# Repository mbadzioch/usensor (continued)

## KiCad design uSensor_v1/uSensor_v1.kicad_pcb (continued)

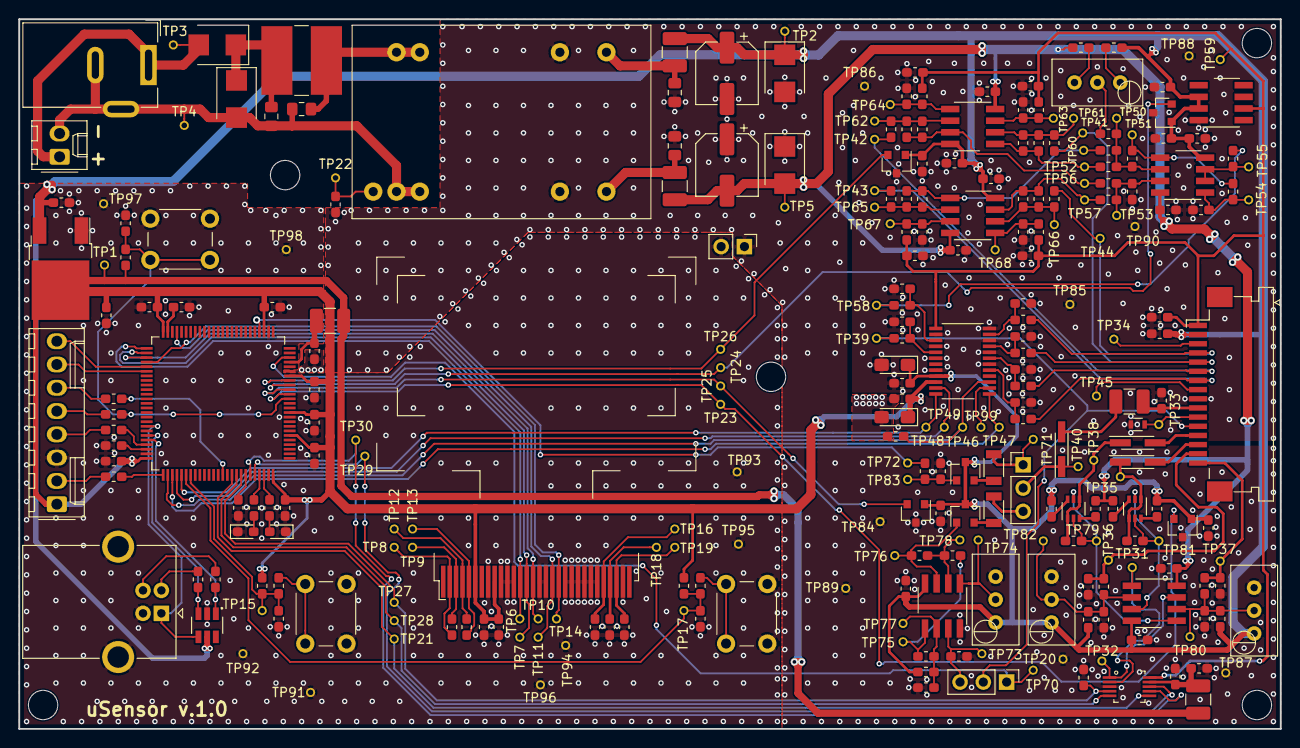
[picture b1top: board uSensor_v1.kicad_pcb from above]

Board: 2 copper layers, 137.6 x 77.4 mm, 295 parts (0 on the bottom side), 134 nets.

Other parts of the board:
Mounting_Hole: MountingHole_3.2mm_M3
Mounting_Hole#2, Mounting_Hole#3, Mounting_Hole#4, Mounting_Hole#5: MountingHole_3.2mm_M3
R52, R59, R60: 10k 1%; R_0603_1608Metric_Pad1.05x0.95mm_HandSolder
R57: 22k 1%; R_0603_1608Metric_Pad1.05x0.95mm_HandSolder
U17: MCP6H02-E/SN; SO-8

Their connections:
-5V: U17.4; also elsewhere on the board
/SENS_IN_AMP_CH_C_D/SENS_OUT_1: U17.1; also elsewhere on the board
/SENS_IN_AMP_CH_C_D/SENS_OUT_2: R57.1, U17.7; also elsewhere on the board
unnamed 46: U17.2; also elsewhere on the board
unnamed 93: U17.5; also elsewhere on the board
SENS_D: R59.2; also elsewhere on the board

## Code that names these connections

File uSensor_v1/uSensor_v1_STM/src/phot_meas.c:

/*
 * multi_adc.c
 *
 *  Created on: 15.07.2018
 *      Author: MCV
 */

#include "stm32f4xx.h"
#include "stm32f4_discovery.h"
#include "diag/Trace.h"
#include <string.h>
#include <stdio.h>
#include <math.h>
#include <phot_meas.h>

#define CHANNELS_NUMBER 4
#define AVERAGE_CYCLES 4
#define BUFFER_SIZE (CHANNELS_NUMBER*AVERAGE_CYCLES)


uint16_t ADC1ConvertedValues[BUFFER_SIZE];
uint8_t phot_transfer_ready_flag=0;


// ******** EXTERNAL ****************
void Photo_Init(void){

	GPIO_InitTypeDef  GPIO_InitStructure;
	SPI_InitTypeDef  SPI_InitStructure;


	/* GPIOG Peripheral clock enable */
	RCC_AHB1PeriphClockCmd(RCC_AHB1Periph_GPIOC, ENABLE);
	RCC_AHB1PeriphClockCmd(RCC_AHB1Periph_GPIOA, ENABLE);

	/* Enable the SPI clock */
	RCC_APB1PeriphClockCmd(RCC_APB1Periph_SPI3,ENABLE);

	/* Configure PC10, PC11 and PC12 in output SCLK, DOUT and DIN  */
	GPIO_InitStructure.GPIO_Pin = GPIO_Pin_10 | GPIO_Pin_11 | GPIO_Pin_12;
	GPIO_InitStructure.GPIO_Mode = GPIO_Mode_AF;
	GPIO_InitStructure.GPIO_OType = GPIO_OType_PP;
	GPIO_InitStructure.GPIO_Speed = GPIO_Speed_100MHz;
	GPIO_InitStructure.GPIO_PuPd = GPIO_PuPd_DOWN;
	GPIO_Init(GPIOC, &GPIO_InitStructure);

	GPIO_PinAFConfig(GPIOC, GPIO_PinSource10, GPIO_AF_SPI3);
	GPIO_PinAFConfig(GPIOC, GPIO_PinSource11, GPIO_AF_SPI3);
	GPIO_PinAFConfig(GPIOC, GPIO_PinSource12, GPIO_AF_SPI3);

	/* Configure PA15 in output CS_neg */
	GPIO_InitStructure.GPIO_Pin = GPIO_Pin_15;
	GPIO_InitStructure.GPIO_Mode = GPIO_Mode_OUT;
	GPIO_InitStructure.GPIO_OType = GPIO_OType_PP;
	GPIO_InitStructure.GPIO_Speed = GPIO_Speed_100MHz;
	GPIO_InitStructure.GPIO_PuPd = GPIO_PuPd_UP;
	GPIO_Init(GPIOA, &GPIO_InitStructure);

	/* Set hight state to CS */
	GPIO_SetBits(GPIOA, GPIO_Pin_15);

	/* SPI configuration -------------------------------------------------------*/
	SPI_I2S_DeInit(SPI1);
	SPI_InitStructure.SPI_Direction = SPI_Direction_2Lines_FullDuplex;
	SPI_InitStructure.SPI_DataSize = SPI_DataSize_16b;
	SPI_InitStructure.SPI_CPOL = SPI_CPOL_Low;
	SPI_InitStructure.SPI_CPHA = SPI_CPHA_1Edge;
	SPI_InitStructure.SPI_NSS = SPI_NSS_Soft;
	SPI_InitStructure.SPI_BaudRatePrescaler = SPI_BaudRatePrescaler_128;
	SPI_InitStructure.SPI_FirstBit = SPI_FirstBit_MSB;
	SPI_InitStructure.SPI_CRCPolynomial = 7;
	SPI_InitStructure.SPI_Mode = SPI_Mode_Master;
	SPI_Init(SPI3, &SPI_InitStructure);

	/* Enable the SPI peripheral */
	SPI_Cmd(SPI1, ENABLE);
}


// ******** INTERNAL ****************

int8_t Spi_GetReg(uint8_t reg)
{
	uint16_t data;

	data=(reg|0x80)<<8;

    GPIO_ResetBits(GPIOA, GPIO_Pin_15);
    while (SPI_I2S_GetFlagStatus(SPI3, SPI_I2S_FLAG_TXE) == RESET);
    SPI_I2S_SendData(SPI3, data);
//	    while(SPI_I2S_GetFlagStatus(SPI1,SPI_I2S_FLAG_TXE)==0);
//	    SPI_I2S_ReceiveData(SPI1);
//	    SPI_I2S_SendData(SPI1, 0xff);
    while (SPI_I2S_GetFlagStatus(SPI3, SPI_I2S_FLAG_RXNE) == RESET);
    data = SPI_I2S_ReceiveData(SPI3);
    GPIO_SetBits(GPIOA, GPIO_Pin_15);

    return data;
}
void Spi_Send(uint8_t reg, uint8_t data)
{
	uint16_t temp;

	temp = reg;
	temp = temp << 8;
	temp |= data;
	temp &= ~0x8000;

    GPIO_ResetBits(GPIOA, GPIO_Pin_15);
    while (SPI_I2S_GetFlagStatus(SPI3, SPI_I2S_FLAG_TXE) == RESET);
    SPI_I2S_SendData(SPI3, temp);
//	    while(SPI_I2S_GetFlagStatus(SPI1,SPI_I2S_FLAG_TXE)==0);
//	    SPI_I2S_ReceiveData(SPI1);
//	    SPI_I2S_SendData(SPI1, 0xff);
    while (SPI_I2S_GetFlagStatus(SPI3, SPI_I2S_FLAG_RXNE) == RESET);
    SPI_I2S_ReceiveData(SPI3);
    GPIO_SetBits(GPIOA, GPIO_Pin_15);
}
void Spi_Read(int8_t* x, int8_t* y, int8_t* z){


	*x = Spi_GetReg(0x29);
	*y = Spi_GetReg(0x2B);
	*z = Spi_GetReg(0x2D);
}


////////////////////////////////////////////////////////////////////////////////////////////




//void PHOT_Init(void){
//	ADC_InitTypeDef       ADC_InitStruct;
//	ADC_CommonInitTypeDef ADC_CommonInitStruct;
//	DMA_InitTypeDef       DMA_InitStruct;
//	GPIO_InitTypeDef      GPIO_InitStruct;
//	NVIC_InitTypeDef NVIC_InitStruct;
//
//	/* Enable ADC1, DMA2 and GPIO clocks ****************************************/
//	RCC_AHB1PeriphClockCmd(RCC_AHB1Periph_DMA2 | RCC_AHB1Periph_GPIOC | RCC_AHB1Periph_GPIOA, ENABLE);
//	RCC_APB2PeriphClockCmd(RCC_APB2Periph_ADC1, ENABLE);//ADC1 is connected to the APB2 peripheral bus
//
//	/* DMA2 Stream0 channel0 configuration **************************************/
//	DMA_InitStruct.DMA_Channel = DMA_Channel_0;
//	DMA_InitStruct.DMA_PeripheralBaseAddr = (uint32_t)&ADC1->DR;//ADC1's data register
//	DMA_InitStruct.DMA_Memory0BaseAddr = (uint32_t)&ADC1ConvertedValues;
//	DMA_InitStruct.DMA_DIR = DMA_DIR_PeripheralToMemory;
//	DMA_InitStruct.DMA_BufferSize = BUFFER_SIZE;
//	DMA_InitStruct.DMA_PeripheralInc = DMA_PeripheralInc_Disable;
//	DMA_InitStruct.DMA_MemoryInc = DMA_MemoryInc_Enable;
//	DMA_InitStruct.DMA_PeripheralDataSize = DMA_PeripheralDataSize_HalfWord;//Reads 16 bit values
//	DMA_InitStruct.DMA_MemoryDataSize = DMA_MemoryDataSize_HalfWord;//Stores 16 bit values
//	DMA_InitStruct.DMA_Mode = DMA_Mode_Circular;
//	DMA_InitStruct.DMA_Priority = DMA_Priority_High;
//	DMA_InitStruct.DMA_FIFOMode = DMA_FIFOMode_Disable;
//	DMA_InitStruct.DMA_FIFOThreshold = DMA_FIFOThreshold_HalfFull;
//	DMA_InitStruct.DMA_MemoryBurst = DMA_MemoryBurst_Single;
//	DMA_InitStruct.DMA_PeripheralBurst = DMA_PeripheralBurst_Single;
//	DMA_Init(DMA2_Stream0, &DMA_InitStruct);
//	DMA_Cmd(DMA2_Stream0, ENABLE);
//
//	/* Configure GPIO pins ******************************************************/
//	GPIO_InitStruct.GPIO_Pin = GPIO_Pin_0 | GPIO_Pin_1 | GPIO_Pin_2 | GPIO_Pin_3;// PC0, PC1, PC2, PC3
//	GPIO_InitStruct.GPIO_Mode = GPIO_Mode_AN;//The pins are configured in analog mode
//	GPIO_InitStruct.GPIO_PuPd = GPIO_PuPd_NOPULL ;//We don't need any pull up or pull down
//	GPIO_InitStruct.GPIO_Speed = GPIO_High_Speed;
//	GPIO_Init(GPIOC, &GPIO_InitStruct);//Initialize GPIOC pins with the configuration
//	GPIO_InitStruct.GPIO_Pin = GPIO_Pin_1;//PA1
//	GPIO_Init(GPIOA, &GPIO_InitStruct);//Initialize GPIOA pins with the configuration
//
//	/* ADC Common Init **********************************************************/
//	ADC_CommonInitStruct.ADC_Mode = ADC_Mode_Independent;
//	ADC_CommonInitStruct.ADC_Prescaler = ADC_Prescaler_Div2;
//	ADC_CommonInitStruct.ADC_DMAAccessMode = ADC_DMAAccessMode_Disabled;
//	ADC_CommonInitStruct.ADC_TwoSamplingDelay = ADC_TwoSamplingDelay_5Cycles;
//	ADC_CommonInit(&ADC_CommonInitStruct);
//
//	/* ADC1 Init ****************************************************************/
//	ADC_DeInit();
//	ADC_InitStruct.ADC_Resolution = ADC_Resolution_12b;//Input voltage is converted into a 12bit int (max 4095)
//	ADC_InitStruct.ADC_ScanConvMode = ENABLE;//The scan is configured in multiple channels
//	ADC_InitStruct.ADC_ContinuousConvMode = ENABLE;//Continuous conversion: input signal is sampled more than once
//	ADC_InitStruct.ADC_ExternalTrigConv = 0;
//	ADC_InitStruct.ADC_ExternalTrigConvEdge = ADC_ExternalTrigConvEdge_None;
//	ADC_InitStruct.ADC_DataAlign = ADC_DataAlign_Right;//Data converted will be shifted to right
//	ADC_InitStruct.ADC_NbrOfConversion = CHANNELS_NUMBER;
//	ADC_Init(ADC1, &ADC_InitStruct);//Initialize ADC with the configuration
//
//	/* Select the channels to be read from **************************************/
//	ADC_RegularChannelConfig(ADC1, ADC_Channel_10, 1, ADC_SampleTime_144Cycles);//PC0
//	ADC_RegularChannelConfig(ADC1, ADC_Channel_11, 2, ADC_SampleTime_144Cycles);//PC1
//	ADC_RegularChannelConfig(ADC1, ADC_Channel_12, 3, ADC_SampleTime_144Cycles);//PC2
//	ADC_RegularChannelConfig(ADC1, ADC_Channel_13, 4, ADC_SampleTime_144Cycles);//PC3
//
//
//
//	NVIC_InitStruct.NVIC_IRQChannel = DMA2_Stream0_IRQn;
//	NVIC_InitStruct.NVIC_IRQChannelCmd = ENABLE;
//	NVIC_InitStruct.NVIC_IRQChannelPreemptionPriority = 3;
//	NVIC_InitStruct.NVIC_IRQChannelSubPriority = 1;
//	NVIC_Init(&NVIC_InitStruct);
//
//	/* Enable DMA request after last transfer (Single-ADC mode) */
//	ADC_DMARequestAfterLastTransferCmd(ADC1, ENABLE);
//
//	//DMA_ITConfig(DMA2_Stream0, DMA_IT_TC, ENABLE);
//
//
//	/* Enable ADC1 DMA */
//	ADC_DMACmd(ADC1, ENABLE);
//
//	/* Enable ADC1 */
//	ADC_Cmd(ADC1, ENABLE);
//
//	/* Start ADC1 Software Conversion */
//	ADC_SoftwareStartConv(ADC1);
//}
//
//
////void DMA2_Stream0_IRQHandler()
////{
////	if(DMA_GetITStatus(DMA2_Stream0, DMA_IT_TC)!= RESET){
////		 DMA_ClearITPendingBit(DMA2_Stream0, DMA_IT_TC);
////		 phot_transfer_ready_flag=1;
////		}
////}

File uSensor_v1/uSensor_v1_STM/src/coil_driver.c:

/*
 * i2c_fun.c
 *
 *  Created on: 15.07.2018
 *      Author: MCV
 */

#include <coil_driver.h>
#include "stm32f4xx.h"


#define I2C_TRANSMITTER_MODE   1
#define I2C_RECEIVER_MODE      0
#define I2C_ACK_ENABLE         1
#define I2C_ACK_DISABLE        0

#define DAC_SCL GPIO_Pin_8		//Port B
#define DAC_SDA GPIO_Pin_9		//Port B
#define DAC_ADDR GPIO_Pin_5		//Port B
#define DAC_CRL_neg GPIO_Pin_6		//Port B
#define DAC_LDAC_neg GPIO_Pin_7		//Port B

#define I2C_TIMEOUT 0xFFFF


uint32_t I2C_Timeout;

static	uint8_t TM_I2C_Stop(I2C_TypeDef* I2Cx);
static 	uint8_t TM_I2C_ReadNack(I2C_TypeDef* I2Cx);
static 	uint8_t TM_I2C_ReadAck(I2C_TypeDef* I2Cx);
static 	void TM_I2C_WriteData(I2C_TypeDef* I2Cx, uint8_t data);
static 	int16_t TM_I2C_Start(I2C_TypeDef* I2Cx, uint8_t address, uint8_t direction, uint8_t ack);
static 	void TM_I2C_Write(I2C_TypeDef* I2Cx, uint8_t address, uint8_t command, uint8_t data_msb, uint8_t data_lsb);
static 	void TM_I2C_ReadMultiNoRegister(I2C_TypeDef* I2Cx, uint8_t address, uint8_t* data, uint16_t count);
static 	uint8_t TM_I2C_ReadNoRegister(I2C_TypeDef* I2Cx, uint8_t address);
static 	void TM_I2C_ReadMulti(I2C_TypeDef* I2Cx, uint8_t address, uint8_t reg, int8_t* data, uint16_t count);
static 	uint8_t TM_I2C_Read(I2C_TypeDef* I2Cx, uint8_t address, uint8_t reg);

// Externals:
// [0 0 0 1 1 A1 A0 R/W]
// Device Address Selection - table 7
// 	ADDR VDD - A1 A0 - 			00
// 	ADDR no connection A1 A0 - 	10
// 	ADDR GND - A1 A0 - 			11
// Write operation R/W = 		0
// first byte - 				0x1C

// [ 0 S C2 C1 C0 A2 A1 A0]
// S - multiple bite operation, set 0 for single write
// Command definition C2 C1 C0 - table 8
//	Write to input register n -								000
// 	Update DAC register n - 								001
// 	Write to input register n, update all (software LDAC) - 010
// 	Write to and update DAC channel n -						011
// 	Power up/power down - 									100
// 	Reset - 												101
// 	LDAC register setup - 									110
// 	Internal reference setup (on/off) - 					111
// DAC Adress Command A2 A1 A0 - table 9
// 	DAC_A -			000
// 	DAC_B - 		001
//  Both DACs -		111
// second byte (write to input, DAC_A) - 0x80
// 3rd and 4th - data

uint8_t DAC_SetVoltage(uint16_t volt)
{

	TM_I2C_Write(I2C1,0x1C,0x80,(uint8_t)(volt>>8),(uint8_t)volt);
	return 1;

}

void DAC_OUT_Coil_Ctrl_Init(void)
{
	GPIO_InitTypeDef GPIO_InitStructure;
	I2C_InitTypeDef I2C_InitStructure;

	RCC_AHB1PeriphClockCmd(RCC_AHB1Periph_GPIOB, ENABLE);
	RCC_APB1PeriphClockCmd(RCC_APB1Periph_I2C1,ENABLE);

	GPIO_StructInit(&GPIO_InitStructure);
	GPIO_InitStructure.GPIO_Pin = DAC_SCL|DAC_SDA|DAC_ADDR|DAC_CRL_neg|DAC_LDAC_neg;
	GPIO_InitStructure.GPIO_Mode = GPIO_Mode_AF;
	GPIO_InitStructure.GPIO_Speed = GPIO_Speed_100MHz;
	GPIO_InitStructure.GPIO_OType = GPIO_OType_OD;
	GPIO_InitStructure.GPIO_PuPd = GPIO_PuPd_NOPULL;
	GPIO_Init(GPIOB, &GPIO_InitStructure);

	GPIO_PinAFConfig(GPIOB,GPIO_PinSource8,GPIO_AF_I2C1);
	GPIO_PinAFConfig(GPIOB,GPIO_PinSource9,GPIO_AF_I2C1);

	I2C_DeInit(I2C1);

	I2C_AnalogFilterCmd(I2C1,ENABLE);
	I2C_DigitalFilterConfig(I2C1,0x0F);

	I2C_StructInit(&I2C_InitStructure);
	I2C_InitStructure.I2C_ClockSpeed=400000;		//Fast mode 400kHz
	I2C_InitStructure.I2C_Mode=I2C_Mode_I2C;
	I2C_InitStructure.I2C_DutyCycle=I2C_DutyCycle_16_9;
	I2C_InitStructure.I2C_OwnAddress1=0x00;
	I2C_InitStructure.I2C_Ack=I2C_Ack_Disable;
	I2C_InitStructure.I2C_AcknowledgedAddress=I2C_AcknowledgedAddress_7bit;

	I2C_Cmd(I2C1,DISABLE);
	I2C_Init(I2C1,&I2C_InitStructure);
	I2C_Cmd(I2C1,ENABLE);

//	TM_I2C_Write(I2C1,0xC0,0,0);
}




// Internals:

static	uint8_t TM_I2C_Read(I2C_TypeDef* I2Cx, uint8_t address, uint8_t reg)
{
	uint8_t received_data=0;
	TM_I2C_Start(I2Cx, address, I2C_TRANSMITTER_MODE, I2C_ACK_DISABLE);
	TM_I2C_WriteData(I2Cx, reg);
	TM_I2C_Stop(I2Cx);
	TM_I2C_Start(I2Cx, address, I2C_RECEIVER_MODE, I2C_ACK_DISABLE);
	received_data = TM_I2C_ReadNack(I2Cx);
	return received_data;
}

static	void TM_I2C_ReadMulti(I2C_TypeDef* I2Cx, uint8_t address, uint8_t reg, int8_t* data, uint16_t count)
{
	TM_I2C_Start(I2Cx, address, I2C_TRANSMITTER_MODE, I2C_ACK_ENABLE);
	TM_I2C_WriteData(I2Cx, reg);
	//TM_I2C_Stop(I2Cx);
	TM_I2C_Start(I2Cx, address, I2C_RECEIVER_MODE, I2C_ACK_ENABLE);
	while (count--) {
		if (!count) {
			/* Last byte */
			*data++ = TM_I2C_ReadNack(I2Cx);
		} else {
			*data++ = TM_I2C_ReadAck(I2Cx);
		}
	}
}

static	uint8_t TM_I2C_ReadNoRegister(I2C_TypeDef* I2Cx, uint8_t address)
{
	uint8_t data;
	TM_I2C_Start(I2Cx, address, I2C_RECEIVER_MODE, I2C_ACK_ENABLE);
	/* Also stop condition happens */
	data = TM_I2C_ReadNack(I2Cx);
	return data;
}

static	void TM_I2C_ReadMultiNoRegister(I2C_TypeDef* I2Cx, uint8_t address, uint8_t* data, uint16_t count)
{
	TM_I2C_Start(I2Cx, address, I2C_RECEIVER_MODE, I2C_ACK_ENABLE);
	while (count--) {
		if (!count) {
			/* Last byte */
			*data = TM_I2C_ReadNack(I2Cx);
		} else {
			*data = TM_I2C_ReadAck(I2Cx);
		}
	}
}

static	void TM_I2C_Write(I2C_TypeDef* I2Cx, uint8_t address, uint8_t command, uint8_t data_msb, uint8_t data_lsb)
{
	TM_I2C_Start(I2Cx, address, I2C_TRANSMITTER_MODE, I2C_ACK_DISABLE);
	TM_I2C_WriteData(I2Cx, command);
	TM_I2C_WriteData(I2Cx, data_msb);
	TM_I2C_WriteData(I2Cx, data_lsb);
	TM_I2C_Stop(I2Cx);
}


static	int16_t TM_I2C_Start(I2C_TypeDef* I2Cx, uint8_t address, uint8_t direction, uint8_t ack)
{
	/* Generate I2C start pulse */
	I2Cx->CR1 |= I2C_CR1_START;

	/* Wait till I2C is busy */
	I2C_Timeout = I2C_TIMEOUT;
	while (!(I2Cx->SR1 & I2C_SR1_SB)) {
		if (--I2C_Timeout == 0x00) {
			return 1;
		}
	}

	/* Enable ack if we select it */
	if (ack) {
		I2Cx->CR1 |= I2C_CR1_ACK;
	}

	/* Send write/read bit */
	if (direction == I2C_TRANSMITTER_MODE) {
		/* Send address with zero last bit */
		I2Cx->DR = address & ~I2C_OAR1_ADD0;

		/* Wait till finished */
		I2C_Timeout = I2C_TIMEOUT;
		while (!(I2Cx->SR1 & I2C_SR1_ADDR)) {
			if (--I2C_Timeout == 0x00) {
				return 1;
			}
		}
	}
	if (direction == I2C_RECEIVER_MODE) {
		/* Send address with 1 last bit */
		I2Cx->DR = address | I2C_OAR1_ADD0;

		/* Wait till finished */
		I2C_Timeout = I2C_TIMEOUT;
		while (!I2C_CheckEvent(I2Cx, I2C_EVENT_MASTER_RECEIVER_MODE_SELECTED)) {
			if (--I2C_Timeout == 0x00) {
				return 1;
			}
		}
	}

	/* Read status register to clear ADDR flag */
	I2Cx->SR2;

	/* Return 0, everything ok */
	return 0;
}

static	void TM_I2C_WriteData(I2C_TypeDef* I2Cx, uint8_t data)
{
	/* Wait till I2C is not busy anymore */
	I2C_Timeout = I2C_TIMEOUT;
	while (!(I2Cx->SR1 & I2C_SR1_TXE) && I2C_Timeout) {
		I2C_Timeout--;
	}

	/* Send I2C data */
	I2Cx->DR = data;
}

static	uint8_t TM_I2C_ReadAck(I2C_TypeDef* I2Cx)
{
	uint8_t data;

	/* Enable ACK */
	I2Cx->CR1 |= I2C_CR1_ACK;

	/* Wait till not received */
	I2C_Timeout = I2C_TIMEOUT;
	while (!I2C_CheckEvent(I2Cx, I2C_EVENT_MASTER_BYTE_RECEIVED)) {
		if (--I2C_Timeout == 0x00) {
			return 1;
		}
	}

	/* Read data */
	data = I2Cx->DR;

	/* Return data */
	return data;
}

static	uint8_t TM_I2C_ReadNack(I2C_TypeDef* I2Cx)
{
	uint8_t data;

	/* Disable ACK */
	I2Cx->CR1 &= ~I2C_CR1_ACK;

	/* Generate stop */
	I2Cx->CR1 |= I2C_CR1_STOP;

	/* Wait till received */
	I2C_Timeout = I2C_TIMEOUT;
	while (!I2C_CheckEvent(I2Cx, I2C_EVENT_MASTER_BYTE_RECEIVED)) {
		if (--I2C_Timeout == 0x00) {
			return 1;
		}
	}

	/* Read data */
	data = I2Cx->DR;

	/* Return data */
	return data;
}

static	uint8_t TM_I2C_Stop(I2C_TypeDef* I2Cx)
{
	/* Wait till transmitter not empty */
	I2C_Timeout = I2C_TIMEOUT;
	while (((!(I2Cx->SR1 & I2C_SR1_TXE)) || (!(I2Cx->SR1 & I2C_SR1_BTF)))) {
		if (--I2C_Timeout == 0x00) {
			return 1;
		}
	}

	/* Generate stop */
	I2Cx->CR1 |= I2C_CR1_STOP;

	/* Return 0, everything ok */
	return 0;
}

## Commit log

2018-11-15 Connector added
2018-12-16 Symulacja + wstepna wersja schematu
2018-12-27 @MWloch - Baseline schematu z wstepnym sterownikiem lasera, cewek i ukladem pomiarowym
2018-12-27 Poprawiono sterowanie cewek
    Dodano szkic pomiaru na fotodiodach
2019-01-05 Dodano wszystkie uklady wejsciowe dla sygnalow fotodiod
2019-01-07 Schematic in progress.
2019-01-10 Added testpoints to schematic.
2019-01-10 Added OLED FP.
2019-01-12 Schematic checked.
2019-01-14 Layout in progress.
2019-01-14 Before schematic changing.
2019-01-14 Schematic changed (added 2channel opamp in one HS)
2019-01-16 Layout improving.
2019-01-17 Connection done.
2019-01-17 Layout ready to 1st review.
2019-01-21 Review.
2019-01-22 Layout correction in progress.
2019-01-24 Layout in progress: before DAC connection changing.
2019-01-29 bEFORE CHECKLIST.
2019-01-29 Components checked.
2019-01-29 Layout in progress (adding vias)
2019-01-29 Added vias.
2019-01-29 Removed designators (without testpoints)
2019-01-29 Ready to final accepting.
2019-01-29 Gerbers Generated.
2019-02-04 Unificated some components. Order ready.
2019-02-28 soft STM32f401
2019-03-01 update 2
